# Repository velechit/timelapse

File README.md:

# Timelapse Timer

Photography Timer based on Atmega8 controller,  OLED display and button controls.

## Specialities:

* USB Based boot loader (based on [baerwolf](https://github.com/baerwolf/USBaspLoader)'s code)
* Minimalsitic SSD1306 driver
* SoftSwitch power on

This project contains Circuit Schematic, PCB Layout, bootloader (Customized), Main Application

This project demonstrates using linker scripts to place code bases at specific location and re-using them across different codes
* Bootloader also implements a minimalistic SSD1306 driver. As the bootloader space in ATMEGA8 is limited to 2k (start address `0x1800`), the driver is placed at `0x1600` which can be accessed through absolute addressing
* The application program (the actual timelapse code) makes use of this SSD1306 driver through absolute addressing
## Progress so far

- [x] Bootloader
- [x] SSD1306 Driver
- [x] Integrate SSD1306 Driver with bootloader, and display a USB icon when in boot load mode
- [x] Update Makefile for bootloader to generate liner script for display driver entry points to be accessed by application program
- [x] Design the PCB
- [x] Get PCB Fabricated
- [x] Framework for the application
- [ ] Main application program

<br/>

**UPDATE 1: Added power off code in bootloader**

**UPDATE 2: Initial dummy firmware implemented which is simple counter**

**UPDATE 3: got the fabricated PCB, assembled, and uploaded the bootloader & the dummy firmware... till now all working**

**UPDATE 4: Framework for main application ready**

<br/>

 _I thought of fabricating the board myself. Due to insufficient time, I have ordered from online fab. I had two options for shipment either too expencive and fast delivery or too slow with easy on pockets. I have chosen the latter, waiting for the board to arrive_

**IMPORTANT Update : I found a issue with the power on circuitory that the internal IO driver transistor is too leakey and is permanently turning on the PMOS power gate. Hence I have added additional NMOS (`2n7002`) to ground externally**

## Toolchain needed
The bootloader and firmware are developed using barebone `avr-gcc` and `avr-libc`

Install `avr-gcc` and `avr-libc`. Under Windows you may chose to use [WinAVR](http://winavr.sourceforge.net/).

Under linux (`Ubuntu` epsecially)
> `sudo apt install gcc-avr avr-libc`

You will also need gmake (generally part of the installation). If not, install using
> `sudo apt install make`

Compile using `make`

### Fuse Settings
The board is designed with external oscillator module. Hence the below fuse settings are used for `Atmega8`

```
lfuse: 1 1 0 0 0 0 0 0 = 0xC0
       | | | | | | | |
       | | | | | | | +- CKSEL0   - External Clock
       | | | | | | +--- CKSEL1
       | | | | | +----- CKSEL2
       | | | | +------- CKSEL3
       | | | +--------- SUT0     - Startup Time 0ms
       | | +----------- SUT1
       | +------------- BODEN    - Brown-out detection disabled
       +--------------- BODLEVEL - Brown-out detection level (N/A)

hfuse: 1 1 0 0 1 0 0 0 = 0xC8
       | | | | | | | |
       | | | | | | | +- BOOTRST  - Reset boots to boot loader
       | | | | | | +--- BOOTSZ0  - Boot section size 2k
       | | | | | +----- BOOTSZ1
       | | | | +------- EESAVE   - No EEPROM save on program
       | | | +--------- CKOPT    - Full Swing Clock
       | | +----------- SPIEN    - Serial programming enabled
       | +------------- WTDON    - Watchdog Timer disabled
       +--------------- RSTDISBL - Reset not disabled
```
Program the above fuses using:

> `avrdude -p atmega8 -P usb -c usbasp -U lfuse:w:0xC0:m -U hfuse:w:0xC8:m`

## Uploading the bootloader
The bootloader and the fuse settings have to be uploaded using any other method of loading (Using Arduino as ISP or USBAsp programmer). Once programmed, the controller can be soldered to the application board and the programmed bootloader be used to upload the main firmware.

## 3D models

<br/>
*3D Model of display side of the board*

<br/>
*3D Model of component side of the board*

## Post Fabrication

<br/>
*Display side of the board*

<br/>
*Component side of the board*

Full documentation can be found [here](https://raw.githack.com/velechit/timelapse/main/board/documentation/index.html)

PCB is designed using 

Download KiCad project files [here](board/timelapse.zip?raw=true)

Schematic can be found [here](board/schematic.pdf?raw=true)

email: elechi@gmail.com

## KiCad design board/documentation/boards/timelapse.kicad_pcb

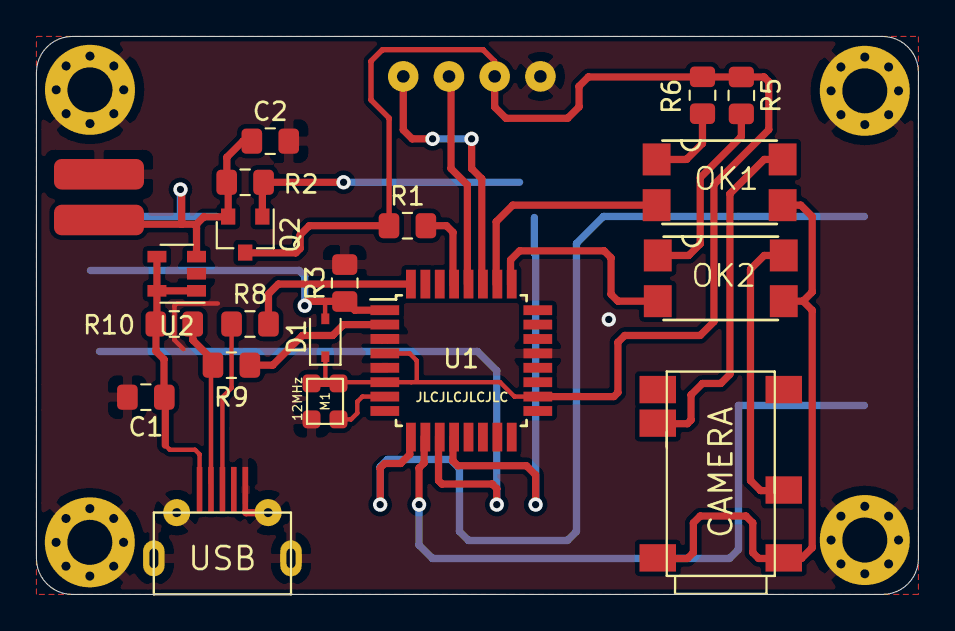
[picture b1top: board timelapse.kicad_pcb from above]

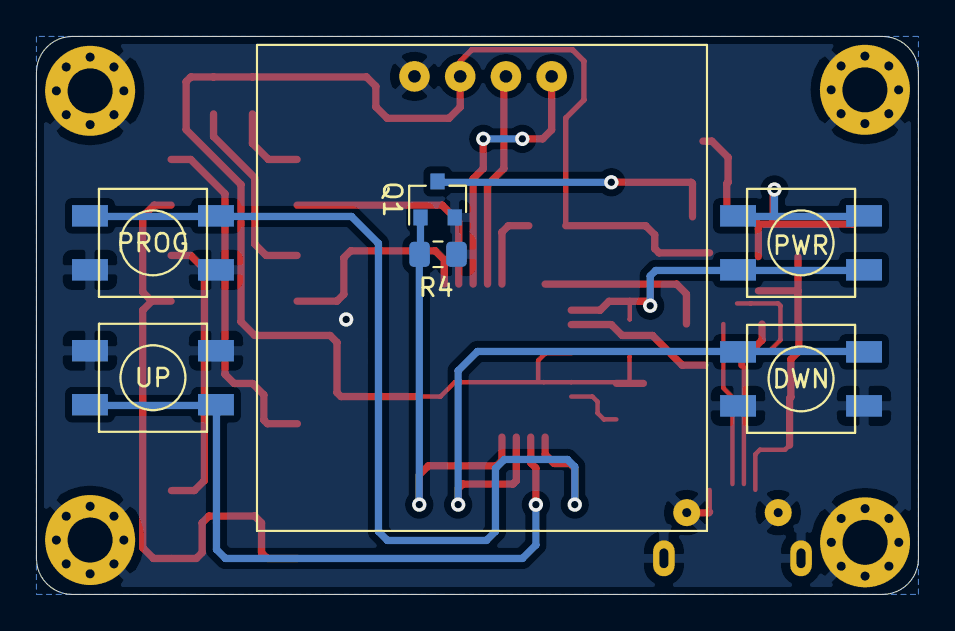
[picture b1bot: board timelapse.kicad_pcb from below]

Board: 2 copper layers, 49.0 x 31.0 mm, 31 parts (7 on the bottom side), 24 nets.

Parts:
C1, C2: 1uF; C_0805_2012Metric_Pad1.15x1.40mm_HandSolder
D1: 1N4148WS; D_SOD-323
H1, H2, H3, H4: MountingHole_Pad; MountingHole_2.5mm_Pad_Via
J1: Battery; PinHeader_1x02_P2.54mm_Vertical
J2: OLED-CONN; OLED-Display-0.96
J3: USB; MICROUSB-V8
M1: 12MHz; SMDXTAL
M2: CAMERA; CAM-CONN-NOKIA
OK1, OK2: PC817SMD; SMD4
Q1: 2N7002; SOT-23
Q2: NDS356; SOT-23
R1: 1k; R_0805_2012Metric_Pad1.15x1.40mm_HandSolder
R2, R3, R4: 10k; R_0805_2012Metric_Pad1.15x1.40mm_HandSolder
R5, R6: 470; R_0805_2012Metric_Pad1.15x1.40mm_HandSolder
R8, R9: 68; R_0805_2012Metric_Pad1.15x1.40mm_HandSolder
R10: 1.5k; R_0805_2012Metric_Pad1.15x1.40mm_HandSolder
SW1: PWR; 4PIN-S
SW2: PROG; 4PIN-S
SW3: UP; 4PIN-S
SW4: DWN; 4PIN-S
U1: ATmega8-16AU; TQFP-32_7x7mm_P0.8mm
U2: MCP73811T; SOT-23-5

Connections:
CAM_CEN: OK2.2, U1.25
CAM_TIP: OK1.2, U1.26
GND: C1.2, C2.2, H1.1, H2.1, H3.1, H4.1, J1.2, J2.1, J3.GND, J3.SHIELD, M1.2, Q1.2, R3.2, R4.2, SW2.P, SW2.P1, SW3.P, SW3.P1, SW4.P, SW4.P1, U1.3, U1.5, U1.21, U2.2
LCD_SCK: J2.3, U1.28
unnamed: J3.D+, R8.1
unnamed: J3.D-, R9.1, R10.2
unnamed: M1.3, U1.7
unnamed: M2.CENTER, OK2.4
unnamed: M2.SHIELD, OK1.3, OK2.3
unnamed: M2.TIP, OK1.4
unnamed: OK1.1, R6.2
unnamed: OK2.1, R5.2
unnamed: Q1.3, Q2.1, R2.2
unnamed: R1.2, U1.29
PW_LATCH: Q1.1, R4.1, U1.12
SW1: D1.2, R3.1, SW1.P, SW1.P1, U1.1
SW2: SW2.S, SW2.S1, U1.9
SW3: SW3.S, SW3.S1, U1.10
SW4: SW4.S, SW4.S1, U1.11
USB_DM: R9.2, U1.2
USB_DP: R8.2, U1.32
VBAT: C2.1, J1.1, Q2.2, R2.1, SW1.S, SW1.S1, U2.3
VCC: D1.1, J2.2, M1.1, M1.4, Q2.3, R1.1, R5.1, R6.1, U1.4, U1.6, U1.18
VUSB: C1.1, J3.VBUS, R10.1, U2.1, U2.4, U2.5

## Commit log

2021-10-28 Adding Bootloader code
2021-10-28 Cleaning up code
2021-10-28 Adding Board Data
2021-10-28 Update documentation
2021-10-28 Fixing Images
2021-10-28 Update ChangeLog
2021-11-10 Fixed schematic and board for power control circuit
    Power Circuit had problem of leaky IO driver nmos within the controller
    added external nmos (2n7002) to take care of proper power on
2021-11-12 Added code in bootloader for power-off
    Power off is added to bootloader based on Timer0
2021-11-12 Adding initial firmware
2021-11-23 updates for main program
2021-11-24 Post Fabrication & Assembly
2021-12-15 Initial Framework of the application firmware
    TODO: Still camera control driver to be written
2021-12-15 Adding e-mail address
2021-12-15 Adding Camera framework
